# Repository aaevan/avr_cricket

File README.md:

#avr_cricket:

This is a thing that pretends to be a cricket. Right now it's only hardware, software to come later.

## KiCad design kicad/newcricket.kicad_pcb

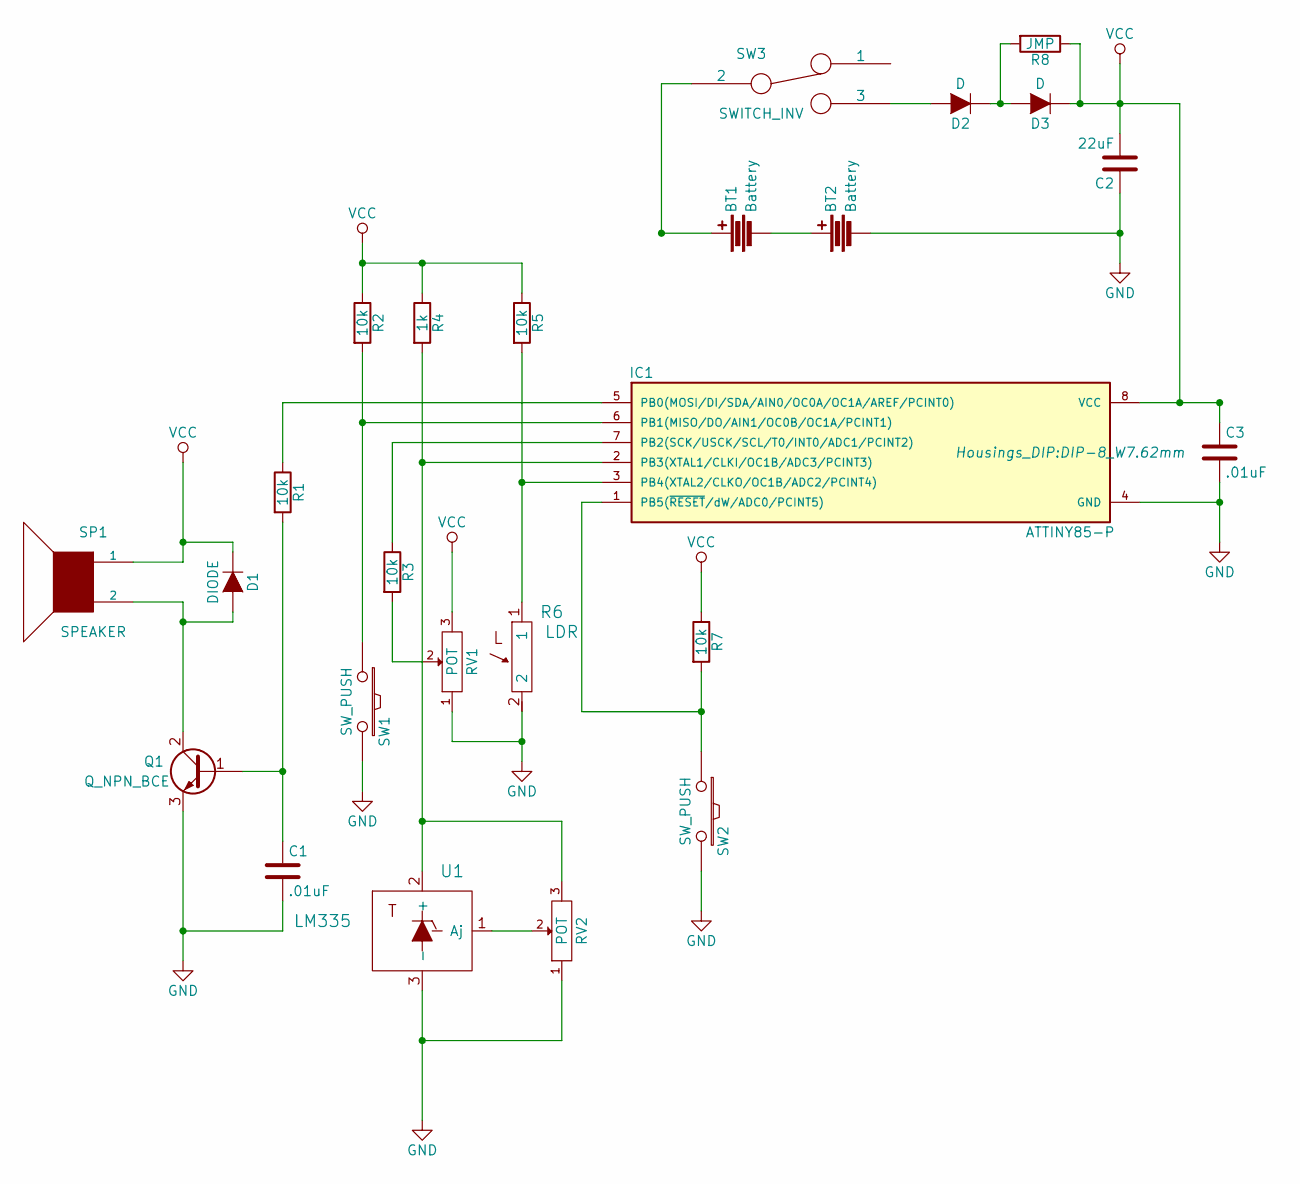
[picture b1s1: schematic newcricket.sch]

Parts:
BT1, BT2: Battery; SMD_cr2032_holder
C1, C3: .01uF; C_1206_HandSoldering
C2: 22uF; C_1210_HandSoldering
D1: DIODE; SOD-323_handsoldering
D2, D3: D; SOD-323_handsoldering
IC1: ATTINY85-P; DIP-8_W7.62mm
Q1: Q_NPN_BCE; SOT-23_Handsoldering
R1, R2, R3, R5, R7: 10k; R_1206_HandSoldering
R4: 1k; R_1206_HandSoldering
R6: LDR
R8: JMP; R_1206_HandSoldering
RV1, RV2: POT; BOURNS-3362P
SP1: SPEAKER; MagneticBuzzer_ProSignal_ABT-410-RC
SW1, SW2: SW_PUSH; SW_SPST_EVPBF
SW3: SWITCH_INV; SW_SPDT_PCM12
U1: LM335; TO-92_Inline_Narrow_Oval

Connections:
GND: BT2.2, C1.2, C2.1, C3.2, IC1.4 (GND), Q1.3 (E), R6.2, RV1.1, RV2.1, SW1.2, SW2.2, U1.3 (-)
unnamed: BT1.1, SW3.2
unnamed: BT1.2, BT2.1
unnamed: C1.1, Q1.1 (B), R1.2
unnamed: D1.2 (A), Q1.2 (C), SP1.2
unnamed: D2.1 (K), D3.2 (A), R8.2
unnamed: D2.2 (A), SW3.3
unnamed: IC1.1 (PB5(~RESET~/dW/ADC0/PCINT5)), R7.2, SW2.1
unnamed: IC1.2 (PB3(XTAL1/CLKI/OC1B/ADC3/PCINT3)), R4.2, RV2.3, U1.2 (+)
unnamed: IC1.3 (PB4(XTAL2/CLKO/OC1B/ADC2/PCINT4)), R5.2, R6.1
unnamed: IC1.5 (PB0(MOSI/DI/SDA/AIN0/OC0A/OC1A/AREF/PCI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), R1.1
unnamed: IC1.6 (PB1(MISO/DO/AIN1/OC0B/OC1A/PCINT1)), R2.2, SW1.1
unnamed: IC1.7 (PB2(SCK/USCK/SCL/T0/INT0/ADC1/PCINT2)), R3.1
unnamed: R3.2, RV1.2
unnamed: RV2.2, U1.1 (Aj)
VCC: C2.2, C3.1, D1.1 (K), D3.1 (K), IC1.8 (VCC), R2.1, R4.1, R5.1, R7.1, R8.1, RV1.3, SP1.1

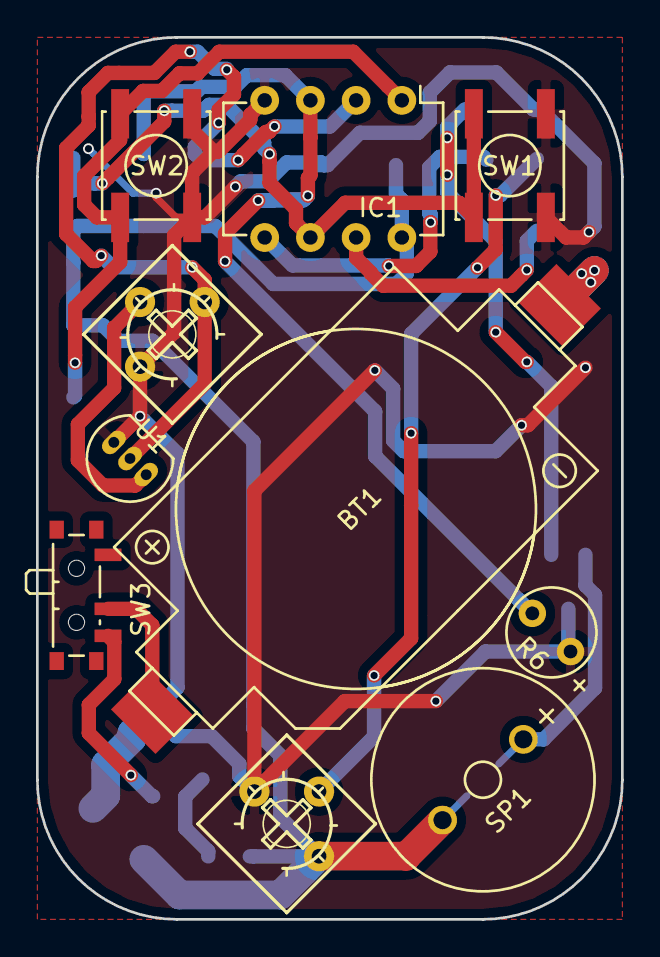
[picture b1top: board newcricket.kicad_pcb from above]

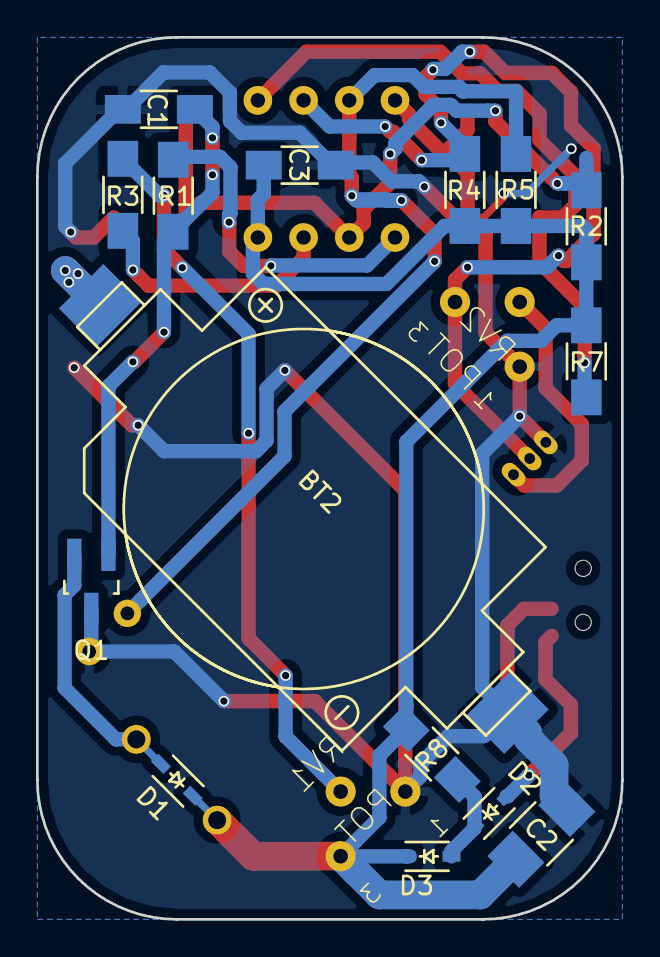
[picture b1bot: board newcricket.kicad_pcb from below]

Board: 2 copper layers, 32.5 x 49.0 mm, 25 parts (15 on the bottom side), 16 nets.

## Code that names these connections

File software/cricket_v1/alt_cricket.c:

// Define clock speed for delay.h:
// (8MHz internal crystal; /8 prescaler): 

#define LED1 PB0 
#define KNOB PB2 
#define F_CPU 1000000L 

#include <avr/io.h> 
#include <util/delay.h> 
#include <avr/interrupt.h>

#define FLAG_NONE 0
#define FLAG_TOGGLE_LED 1

#define CHIRP_LENGTH 1250 //1250
#define CHIRP_PITCH 163 //163 base pitch
#define SUBCHIRP_LENGTH 15 //15

void setFlag(int);
int getFlag();
volatile int flag = FLAG_NONE;

ISR(TIM1_OVF_vect)
{
    TCNT1 = CHIRP_PITCH; //startcount from 200 instead from 0
    setFlag(FLAG_TOGGLE_LED);
}

int main(void)
{
    // make PB0 an output (LED), make PB2 an input (Button)
    DDRB |= (1<<DDB0);
    // turn off LED
    PORTB &= ~(1<<PB0);
    //comparator B output mode pg 89
    TCCR1 &= ~( (1<<COM1A1)|(1<<COM1A0) ); //COM1A1 = 0, COMA10 = 0
    //Comparator b output mode pg 90
    TCCR1 &= ~((1<<COM1B1)|(1<<COM1B0));
    // Timer/Counter1 Prescale Select pg 89
    //TCCR1 |= (1<<CS13)|(1<<CS11);
    TCCR1 |= (1<<CS10);
    TCCR1 &= ~((1<<CS13)|(1<<CS12)|(1<<CS11));
    //TCR1 &= ~((1<<CS11)|1<<CS10));
    //Enable interrupt
    TIMSK |= (1<<TOIE1);
    sei();

    TCNT1 = 0; 

    int i = 0;
    int j = 0;
    int temp_val = analog_read(PB3);
    int temp = 0;
    float temp_c = 0;
    float n_8 = 0;
    float chirps_per_second = 0;
    float delay_time = 0;
    float period = 0;
    
    while(1)
    {
        //TCCR1 &= ~((1<<CS10)|(1<<CS13)|(1<<CS12)|(1<<CS11));
        //TCCR1 |= (1<<CS10);
        //TCCR1 &= ~((1<<CS13)|(1<<CS12)|(1<<CS11));
        if(temp_c > 12.8){
        for(j=0; j<=2; j++)
            {
                for(i=0; i<=CHIRP_LENGTH; i++)
                {
                    if(getFlag() == FLAG_TOGGLE_LED)
                    {
                        PORTB ^= (1<<PB0);
                        setFlag(FLAG_NONE);
                    }
                }
                PORTB &= ~(1<<PB0);
                delay(SUBCHIRP_LENGTH);
            }
        }
        temp_val = analog_read(PB4); //we did have pb3 here before...

        //temp_c = 0.509 * (float) temp_val + 297.57;
        //temp_c = temp_val * 0.0048 * 100 - 273.15;
        temp_c = 24;
        n_8 = temp_c - 5;
        chirps_per_second = n_8 / 8;
        //chirps_per_second = 2.5;
        period = 1.0/chirps_per_second;
        delay_time = 1000.0 * period - 122;

        //delay(delay_time);//800
        delay((int) delay_time);//800
        //40 + N15
        //2.66 + N1 = T(f) - 2.66
        /*
        int temp = analog_read(PB3);
        delay(temp);
        //delay(analog_read(PB4));
        PORTB ^= (1<<PB0);
        */
    }
}


//void tone_delay

void setFlag(int f)
{
    flag = f;
}

int getFlag()
{
    return flag;
}

int analog_read(int read_pin){ 
    //Read ADC2L:
    if(read_pin != 1 && read_pin != 2 && read_pin != 3){
        //if read_pin is not a valid number, break. 
        return 0;
    }
    ADMUX |= read_pin; //set the pin that the adc reads to ADC2 (PB4) 
    ADCSRA |= (1 << ADEN); // Analog-Digital enable bit 
    ADCSRA |= (1 << ADSC); // Discard first conversion 
    while (ADCSRA & (1 << ADSC)); // wait until conversion is done 
    ADCSRA |= (1 << ADSC); // start single conversion 
    while (ADCSRA & (1 << ADSC)) // wait until conversion is done
    ADCSRA &= ~(1<<ADEN); // shut down the ADC
    int low_val = ADCL;
    int high_val = ADCH;
    int val = (high_val<<8)|low_val;
    //Clear bottom 3 bits of ADMUX:
    ADMUX &= ~(0x111);
    return val;
}

void delay_microseconds(int us){
    int i;
    for (i = 0; i < us; i++){
        _delay_us(1);
    }
}

void delay(int ms){
    int i;
    for (i=0; i<ms; i++) {
        _delay_ms(1);
    }
}

void toggle(int pin){
    PORTB ^= (1<<pin);
}

void set_high(int pin){
    PORTB |= (1<<pin);
}

void set_low(int pin){
    PORTB &= ~(1<<pin);
}

/*
int main(void){

    // Setup :
    //Set LED as output:
    DDRB |= (1<<LED1);
    set_high(LED1);
    //default is input, 1 is output.
    // Main:
    int knob_pos;
    while (1){
        knob_pos = analog_read(2);
        delay(knob_pos);
        toggle(LED1);
    }
    return 0;
    *
} 
*/

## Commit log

2015-11-29 First commit: partially completed kicad project.
2015-11-29 Made a few new files and organized things.
2015-11-29 added missing ground
2015-11-29 cleaned up a few traces
2015-12-02 A first version of the board and some changes to the schematic.
2015-12-02 Rearranged some components, soon to start laying traces.
2015-12-02 Most of a layout-- still need to fix the switch so it's connected.
2015-12-02 Still throwing a few errors, filled zone placed. Board looking near-complete.
2015-12-02 Fixed a pad clearance problem near the temperature sensor.
2015-12-02 Schematic file updated: no obvious changes. Had not been saved in a while.
2015-12-02 Fixed the clearances on a filled zone near ATtiny.
2015-12-03 Switched pads 2 and 6.
2015-12-04 Rearranged traces on upper half of board. Also moved around silkscreen labels.
2015-12-04 Minor changes to silkscreens.
2015-12-04 Generated Gerber files.
2015-12-04 Generated Bill of Materials and Gerbers.
2015-12-04 removed old gerbers.
2016-01-03 Board assembled: re-started work on software. Light sensing working. Experiencing strange resetting behavior now.
2016-01-03 Removed some duplicate files.
2016-01-04 WDT is now turned off during chirp().
